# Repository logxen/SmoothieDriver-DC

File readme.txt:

OVERVIEW

SmoothieDriver is a series of motor controllers designed to interface with Smoothieboard and other RepRap style motion controllers, allowing an enable/direction/step interface like the Pololu A4988 breakout boards commonly used and optionally i2c block level control with closed-loop feedback for advanced systems.

SmoothieDriver-DC is a series of Full H-Bridge drivers with closed-loop encoder feedback for driving Brush DC Motors. The system allows Brushed DC Motors to be controlled much like a stepper motor.

The current prototype board (gamma) is a triple motor driver capable of up to 3.5A per motor.

For more information contact Logxen. He is easily found on irc.freenode.net in #smoothieware or by e-mail at reprap at logxen dot com.

MAJOR COMPONENTS

SmoothieDriver-DC Gamma uses an NXP LPC1114, which has an Arm Cortex-M0 core, as mcu. It drives up to three Allegro a4950 full h-bridge drivers with current control managed by an MCP4725 on each driver. An upgrade from the Beta version, Gamma includes an MCP1252 3.3V regulator on-board so that it can be safely driven from a 3.3V or a 5V motion controller.

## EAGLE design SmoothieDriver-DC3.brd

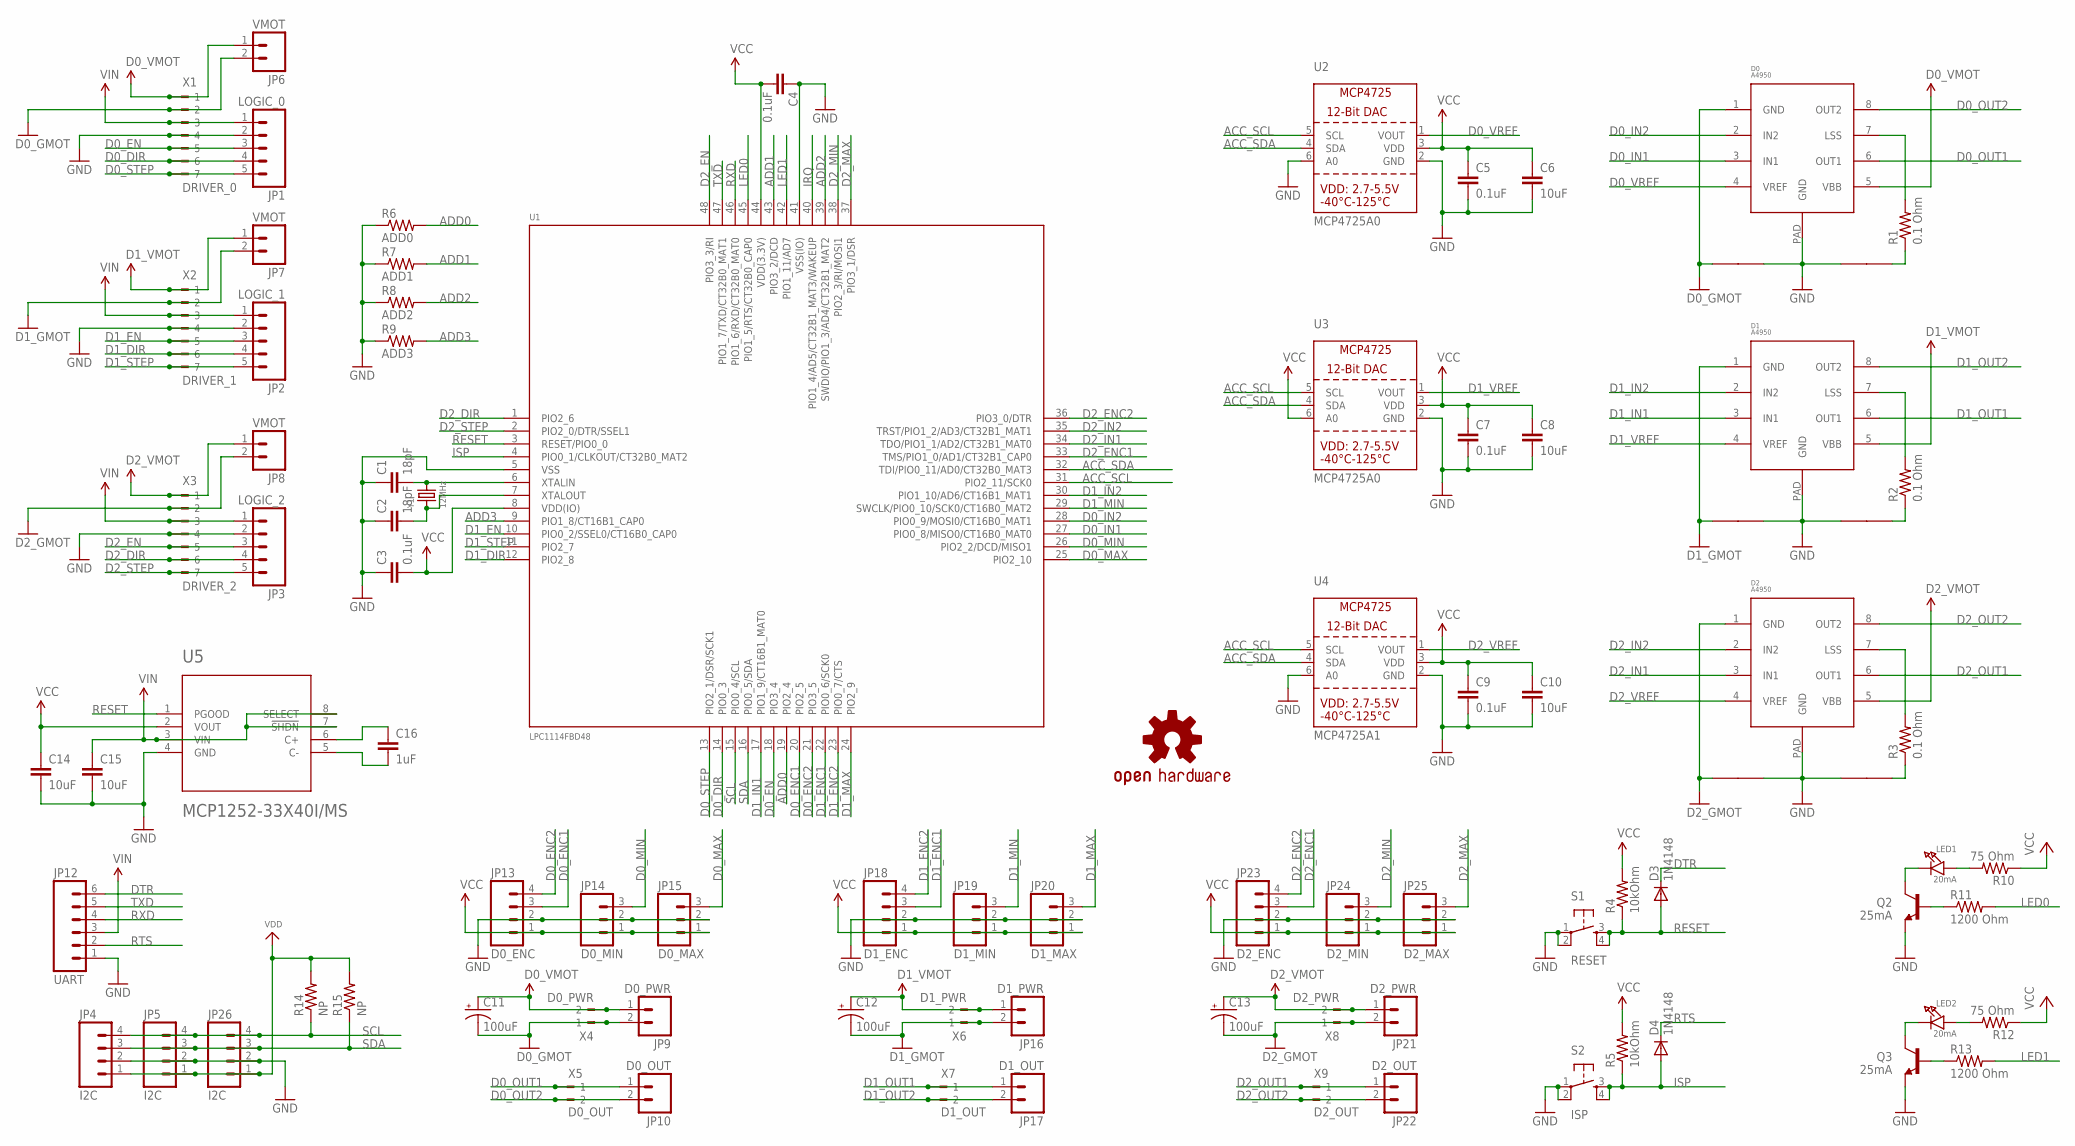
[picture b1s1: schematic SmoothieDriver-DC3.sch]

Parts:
C1, C2: 18pF; 0603-CAP
C3, C4, C5, C7, C9: 0.1uF; 0603-CAP
C6, C8, C10: 10uF; 0603-CAP
C11, C12, C13: 100uF; PANASONIC_E
C14, C15: 10uF; 1206
C16: 1uF; 0805
D0, D1, D2: A4950; SOICN8-PAD
D0_GMOT: NET_LINK
D3, D4: 1N4148; SOD523
JP1: LOGIC_0; 1X05
JP2: LOGIC_1; 1X05
JP3: LOGIC_2; 1X05
JP4, JP5, JP26: I2C; 1X04
JP6, JP7, JP8: VMOT; 1X02
JP9: D0_PWR; 1X02
JP10: D0_OUT; 1X02
JP12: UART; 1X06
JP13: D0_ENC; 1X04
JP14: D0_MIN; 1X03
JP15: D0_MAX; 1X03
JP16: D1_PWR; 1X02
JP17: D1_OUT; 1X02
JP18: D1_ENC; 1X04
JP19: D1_MIN; 1X03
JP20: D1_MAX; 1X03
JP21: D2_PWR; 1X02
JP22: D2_OUT; 1X02
JP23: D2_ENC; 1X04
JP24: D2_MIN; 1X03
JP25: D2_MAX; 1X03
LED1, LED2: 20mA; CHIPLED_0805
Q2, Q3: 25mA; SOT23
R1, R2, R3: 0.1 Ohm; R2512
R4, R5: 10kOhm; 0603-RES
R6: ADD0; 0603-RES
R7: ADD1; 0603-RES
R8: ADD2; 0603-RES
R9: ADD3; 0603-RES
R10, R12: 75 Ohm; R0603
R11, R13: 1200 Ohm; R0603
R14, R15: NP; 0603-RES
S1: RESET; TACTILE_SWITCH_SMD
S2: ISP; TACTILE_SWITCH_SMD
U1: LPC1114FBD48; LQFP48
U2, U3: MCP4725A0; SOT23-6
U4: MCP4725A1; SOT23-6
U5: MCP1252-33X40I/MS; MSOP8_0.65MM
U$15: OSHW-LOGOM; OSHW-LOGO-M
U$22, U$23, U$24, U$25, U$26: NET_LINK
X1: DRIVER_0; 180-7
X2: DRIVER_1; 180-7
X3: DRIVER_2; 180-7
X4: D0_PWR; 180-2
X5: D0_OUT; 180-2
X6: D1_PWR; 180-2
X7: D1_OUT; 180-2
X8: D2_PWR; 180-2
X9: D2_OUT; 180-2
Y1: 12MHz; CRYSTAL_3.2X2.5

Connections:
ACC_SCL: U1.31 (PIO2_11/SCK0), U2.5 (SCL), U3.5 (SCL), U4.5 (SCL)
ACC_SDA: U1.32 (TDI/PIO0_11/AD0/CT32B0_MAT3), U2.4 (SDA), U3.4 (SDA), U4.4 (SDA)
ADD0: R6.2, U1.19 (PIO2_4)
ADD1: R7.2, U1.43 (PIO3_2/DCD)
ADD2: R8.2, U1.39 (SWDIO/PIO1_3/AD4/CT32B1_MAT2)
ADD3: R9.2, U1.9 (PIO1_8/CT16B1_CAP0)
D0_DIR: JP1.4, U1.14 (PIO0_3), X1.6
D0_EN: JP1.3, U1.18 (PIO3_4), X1.5
D0_ENC1: JP13.3, U1.20 (PIO2_5)
D0_ENC2: JP13.4, U1.21 (PIO3_5)
D0_GMOT: C11.-, D0.1 (GND), D0_GMOT.P$1, JP6.2, JP9.2, X1.2, X4.1
D0_IN1: D0.3 (IN1), U1.27 (PIO0_8/MISO0/CT16B0_MAT0)
D0_IN2: D0.2 (IN2), U1.28 (PIO0_9/MOSI0/CT16B0_MAT1)
D0_LSS: D0.7 (LSS), R1.2
D0_MAX: JP15.3, U1.25 (PIO2_10)
D0_MIN: JP14.3, U1.26 (PIO2_2/DCD/MISO1)
D0_OUT1: D0.6 (OUT1), JP10.1, X5.1
D0_OUT2: D0.8 (OUT2), JP10.2, X5.2
D0_STEP: JP1.5, U1.13 (PIO2_1/DSR/SCK1), X1.7
D0_VMOT: C11.+, D0.5 (VBB), JP6.1, JP9.1, X1.1, X4.2
D0_VREF: D0.4 (VREF), U2.1 (VOUT)
D1_DIR: JP2.4, U1.12 (PIO2_8), X2.6
D1_EN: JP2.3, U1.10 (PIO0_2/SSEL0/CT16B0_CAP0), X2.5
D1_ENC1: JP18.3, U1.22 (PIO0_6/SCK0)
D1_ENC2: JP18.4, U1.23 (PIO0_7/CTS)
D1_GMOT: C12.-, D1.1 (GND), JP7.2, JP16.2, U$23.P$1, X2.2, X6.1
D1_IN1: D1.3 (IN1), U1.17 (PIO1_9/CT16B1_MAT0)
D1_IN2: D1.2 (IN2), U1.30 (PIO1_10/AD6/CT16B1_MAT1)
D1_LSS: D1.7 (LSS), R2.2
D1_LSS1: D2.7 (LSS), R3.2
D1_MAX: JP20.3, U1.24 (PIO2_9)
D1_MIN: JP19.3, U1.29 (SWCLK/PIO0_10/SCK0/CT16B0_MAT2)
D1_OUT1: D1.6 (OUT1), JP17.1, X7.1
D1_OUT2: D1.8 (OUT2), JP17.2, X7.2
D1_STEP: JP2.5, U1.11 (PIO2_7), X2.7
D1_VMOT: C12.+, D1.5 (VBB), JP7.1, JP16.1, X2.1, X6.2
D1_VREF: D1.4 (VREF), U3.1 (VOUT)
D2_DIR: JP3.4, U1.1 (PIO2_6), X3.6
D2_EN: JP3.3, U1.48 (PIO3_3/RI), X3.5
D2_ENC1: JP23.3, U1.33 (TMS/PIO1_0/AD1/CT32B1_CAP0)
D2_ENC2: JP23.4, U1.36 (PIO3_0/DTR)
D2_GMOT: C13.-, D2.1 (GND), JP8.2, JP21.2, U$26.P$1, X3.2, X8.1
D2_IN1: D2.3 (IN1), U1.34 (TDO/PIO1_1/AD2/CT32B1_MAT0)
D2_IN2: D2.2 (IN2), U1.35 (TRST/PIO1_2/AD3/CT32B1_MAT1)
D2_MAX: JP25.3, U1.37 (PIO3_1/DSR)
D2_MIN: JP24.3, U1.38 (PIO2_3/RI/MOSI1)
D2_OUT1: D2.6 (OUT1), JP22.1, X9.1
D2_OUT2: D2.8 (OUT2), JP22.2, X9.2
D2_STEP: JP3.5, U1.2 (PIO2_0/DTR/SSEL1), X3.7
D2_VMOT: C13.+, D2.5 (VBB), JP8.1, JP21.1, X3.1, X8.2
D2_VREF: D2.4 (VREF), U4.1 (VOUT)
DTR: D3.C, JP12.6
GND: C1.1, C2.1, C3.1, C4.1, C5.2, C6.2, C7.2, C8.2, C9.2, C10.2, C14.2, C15.2, D0.PAD (GND), D0_GMOT.P$2, D1.PAD (GND), D2.PAD (GND), JP1.2, JP2.2, JP3.2, JP4.2, JP5.2, JP12.1, JP13.2, JP14.2, JP15.2, JP18.2, JP19.2, JP20.2, JP23.2, JP24.2, JP25.2, JP26.2, Q2.2 (E), Q3.2 (E), R1.1, R2.1, R3.1, R6.1, R7.1, R8.1, R9.1, S1.1, S1.2, S2.1, S2.2, U1.5 (VSS), U1.41 (VSS(IO)), U2.2 (GND), U2.6 (A0), U3.2 (GND), U4.2 (GND), U4.6 (A0), U5.4 (GND), U$22.P$1, U$22.P$2, U$23.P$2, U$24.P$1, U$24.P$2, U$25.P$1, U$25.P$2, U$26.P$2, X1.4, X2.4, X3.4
IRQ: U1.40 (PIO1_4/AD5/CT32B1_MAT3/WAKEUP)
ISP: D4.A, R5.1, S2.3, S2.4, U1.4 (PIO0_1/CLKOUT/CT32B0_MAT2)
LED0: R11.2, U1.45 (PIO1_5/RTS/CT32B0_CAP0)
LED1: R13.2, U1.42 (PIO1_11/AD7)
unnamed: LED1.A, R10.2
unnamed: LED1.C, Q2.3 (C)
unnamed: Q2.1 (B), R11.1
unnamed: Q3.1 (B), R13.1
unnamed: LED2.A, R12.2
unnamed: LED2.C, Q3.3 (C)
PWRREG_C+: C16.1, U5.6 (C+)
PWRREG_C-: C16.2, U5.5 (C-)
RESET: D3.A, R4.1, S1.3, S1.4, U1.3 (RESET/PIO0_0), U5.1 (PGOOD)
RTS: D4.C, JP12.2
RXD: JP12.4, U1.46 (PIO1_6/RXD/CT32B0_MAT0)
SCL: JP4.4, JP5.4, JP26.4, R14.1, U1.15 (PIO0_4/SCL)
SDA: JP4.3, JP5.3, JP26.3, R15.1, U1.16 (PIO0_5/SDA)
TXD: JP12.5, U1.47 (PIO1_7/TXD/CT32B0_MAT1)
VCC: C3.2, C4.2, C5.1, C6.1, C7.1, C8.1, C9.1, C10.1, C14.1, JP13.1, JP14.1, JP15.1, JP18.1, JP19.1, JP20.1, JP23.1, JP24.1, JP25.1, R4.2, R5.2, R10.1, R12.1, U1.8 (VDD(IO)), U1.44 (VDD(3.3V)), U2.3 (VDD), U3.3 (VDD), U3.6 (A0), U4.3 (VDD), U5.2 (VOUT)
VDD: JP4.1, JP5.1, JP26.1, R14.2, R15.2
VIN: C15.1, JP1.1, JP2.1, JP3.1, JP12.3, U5.3 (VIN), U5.7 (!SHDN), U5.8 (SELECT), X1.3, X2.3, X3.3
XTALIN: C1.2, U1.6 (XTALIN), Y1.2
XTALOUT: C2.2, U1.7 (XTALOUT), Y1.1

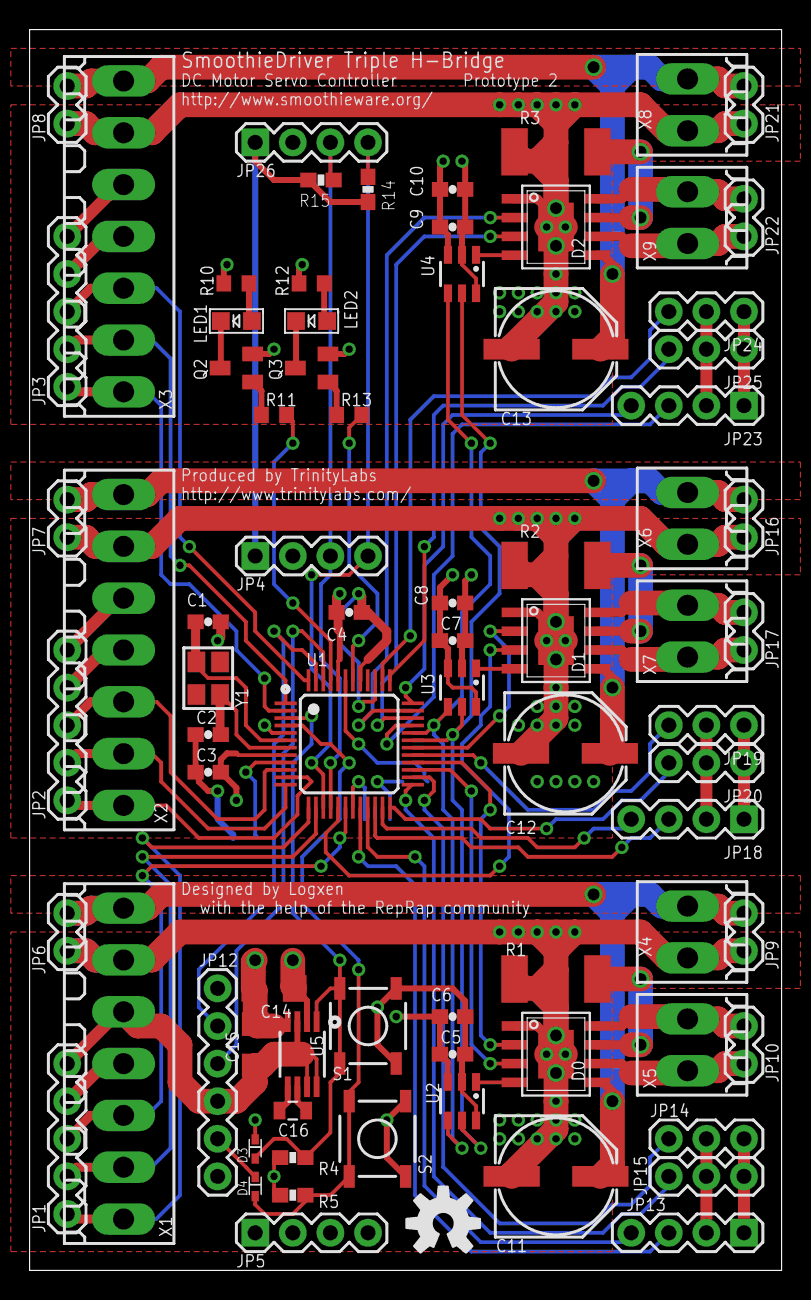
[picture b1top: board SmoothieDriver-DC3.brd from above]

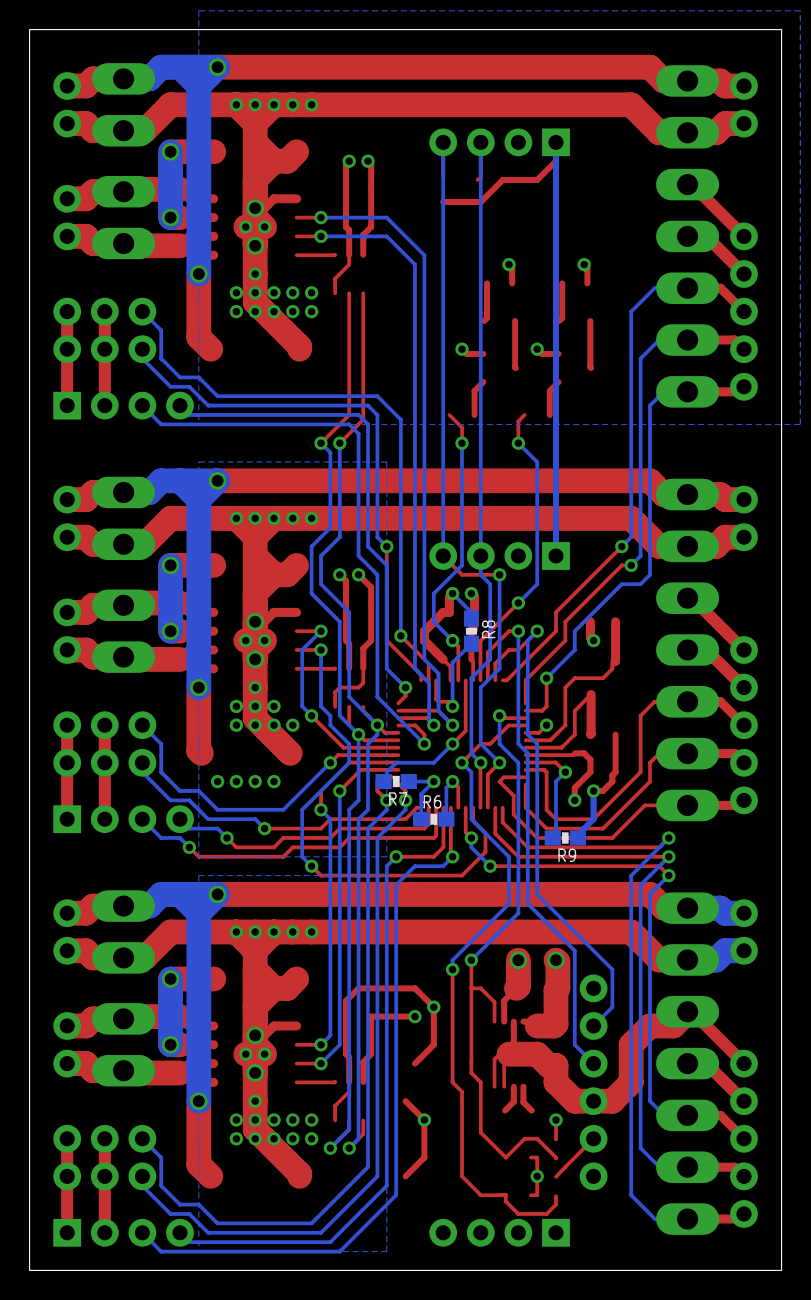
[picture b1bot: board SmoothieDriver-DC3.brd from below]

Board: 4 copper layers, 50.8 x 83.8 mm, 89 parts (5 on the bottom side), 75 nets.

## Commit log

2012-11-21 Innitial commit of DC-3 Gamma board
2012-12-04 Prototype 2 as sent to board house

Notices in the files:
parts and their libraries:
microbuilder: This work is placed in the public domain, and may be freely used for commercial and non-commercial work with the following conditions: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
SparkFun-Capacitors: Licensing: CC v3.0 Share-Alike You are welcome to use this library for commercial purposes.
